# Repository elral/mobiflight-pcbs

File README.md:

# mobiflight-pcbs
PCBs and breakout boards, designed by the MobiFlight community:

* [MobiFlight Prototyping Board](prototyping-board/README.md)
* [MobiFlight Multiplexer Breakout Board](breakout-multiplexer/README.md)
* [MobiFlight MAX7219 Breakout System](max7219-breakout-system/README.md)
* [MobiFlight MAX7219 Adapter Board](max7219-adapter/README.md)
* [MobiFlight Dual Encoder Board](dual-encoder-board/README.md)
* [MobiFlight LED Driver Board](dual-encoder-board/README.md)

If you are missing information, or if you found a bug, please [create a new issue here on GitHub](https://github.com/MobiFlight/mobiflight-pcbs/issues/new).

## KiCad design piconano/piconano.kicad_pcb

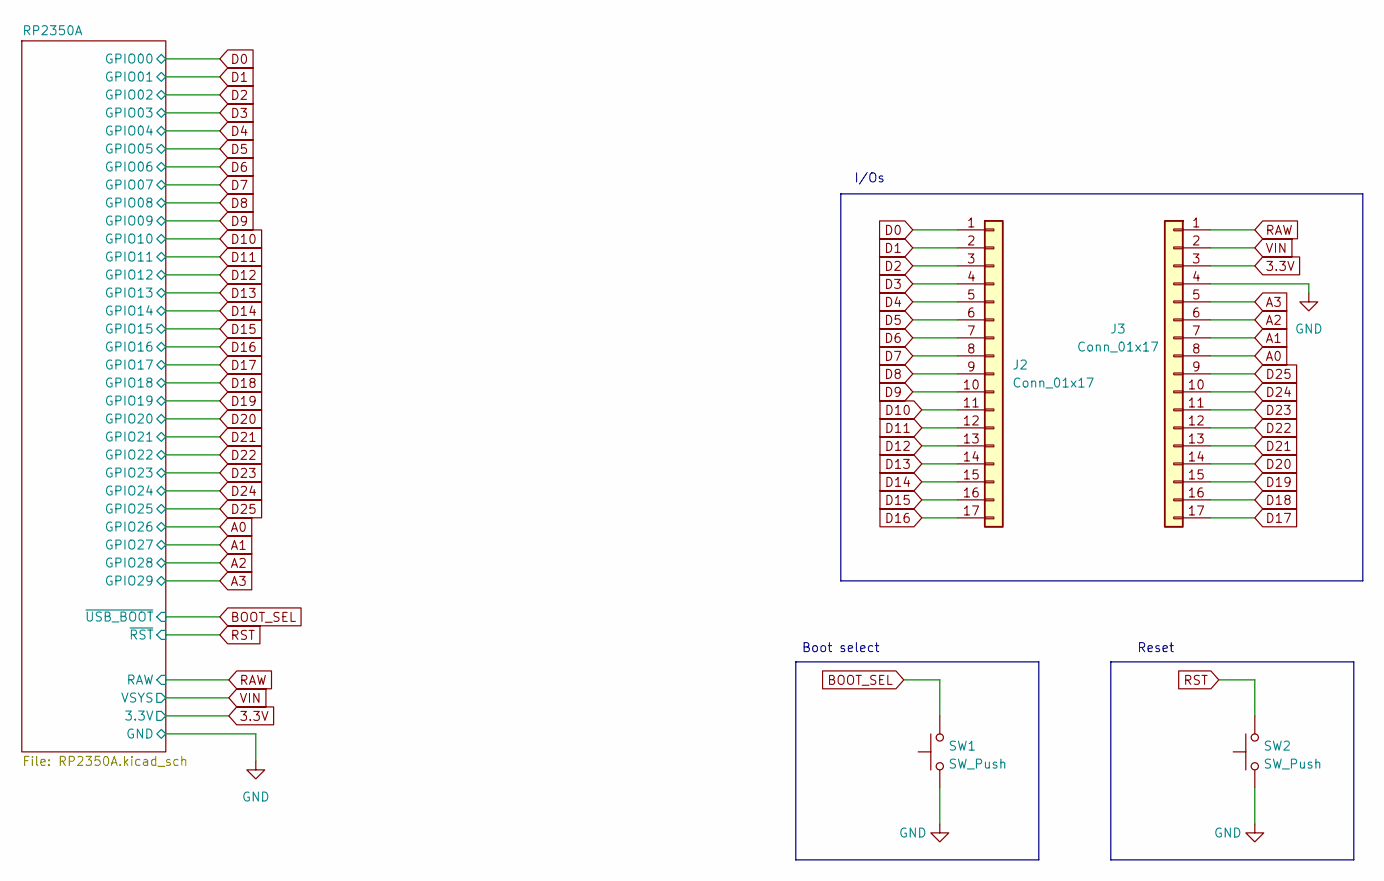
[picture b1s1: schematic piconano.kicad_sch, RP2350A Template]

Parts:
J2, J3: Conn_01x17; PinHeader_1x17_P2.54mm_Vertical
SW1, SW2: SW_Push; SW_Push_1P1T_NO_Vertical_Wuerth_434133025816; LCSC C92589

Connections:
3.3V: J3.3; also elsewhere on the board
A0: J3.8; also elsewhere on the board
A1: J3.7; also elsewhere on the board
A2: J3.6; also elsewhere on the board
A3: J3.5; also elsewhere on the board
BOOT_SEL: SW1.2; also elsewhere on the board
D0: J2.1; also elsewhere on the board
D1: J2.2; also elsewhere on the board
D2: J2.3; also elsewhere on the board
D3: J2.4; also elsewhere on the board
D4: J2.5; also elsewhere on the board
D5: J2.6; also elsewhere on the board
D6: J2.7; also elsewhere on the board
D7: J2.8; also elsewhere on the board
D8: J2.9; also elsewhere on the board
D9: J2.10; also elsewhere on the board
D10: J2.11; also elsewhere on the board
D11: J2.12; also elsewhere on the board
D12: J2.13; also elsewhere on the board
D13: J2.14; also elsewhere on the board
D14: J2.15; also elsewhere on the board
D15: J2.16; also elsewhere on the board
D16: J2.17; also elsewhere on the board
D17: J3.17; also elsewhere on the board
D18: J3.16; also elsewhere on the board
D19: J3.15; also elsewhere on the board
D20: J3.14; also elsewhere on the board
D21: J3.13; also elsewhere on the board
D22: J3.12; also elsewhere on the board
D23: J3.11; also elsewhere on the board
D24: J3.10; also elsewhere on the board
D25: J3.9; also elsewhere on the board
GND: J3.4, SW1.1, SW2.1; also elsewhere on the board
RAW: J3.1; also elsewhere on the board
RST: SW2.2; also elsewhere on the board
VIN: J3.2; also elsewhere on the board

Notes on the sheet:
Reset
Boot select
I/Os

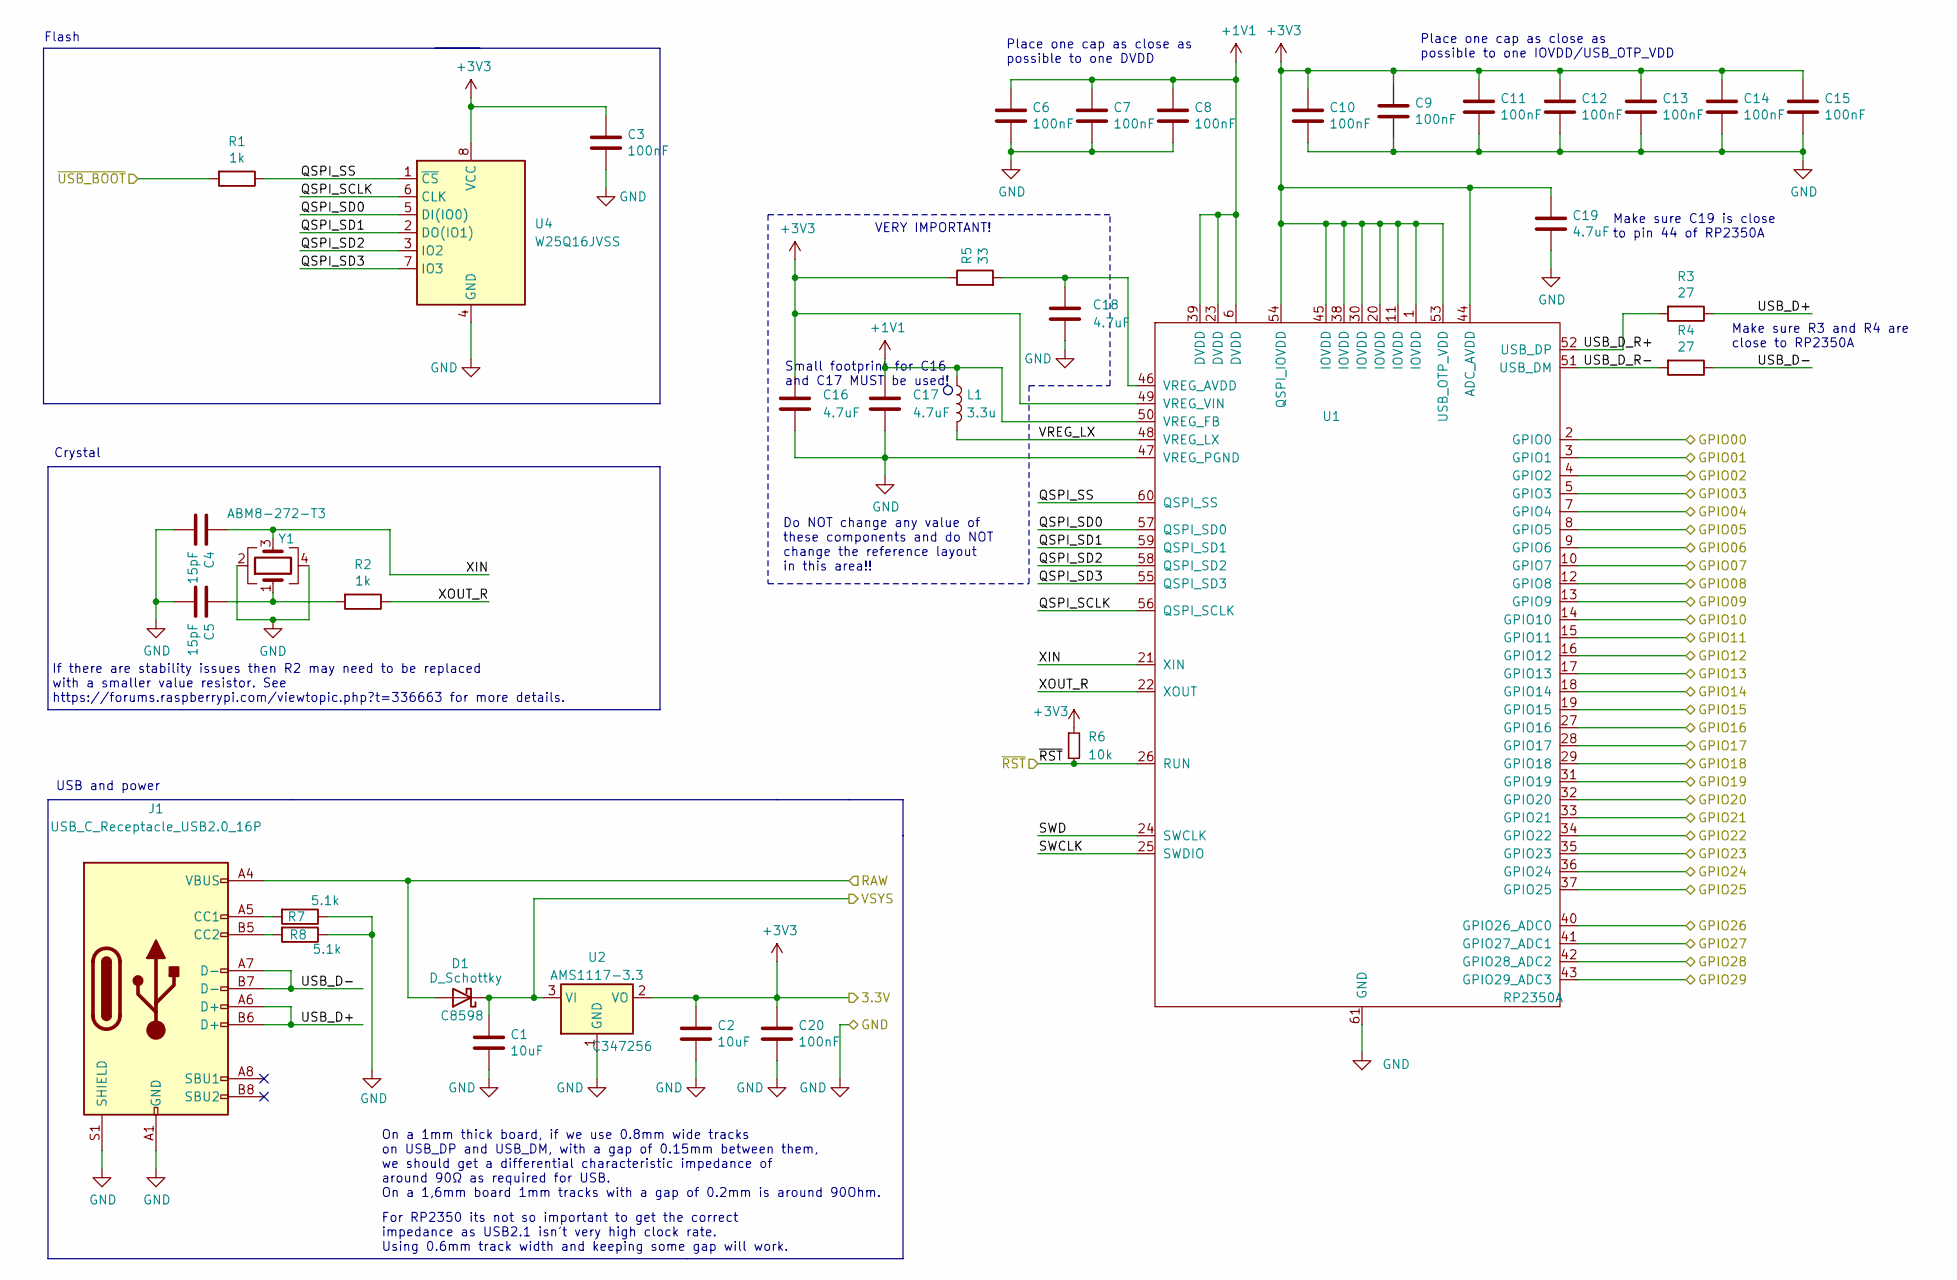
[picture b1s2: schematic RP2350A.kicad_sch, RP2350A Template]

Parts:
C1, C2: 10uF; C_0402_1005Metric; LCSC C15525
C3, C6, C7, C8, C9, C10, C11, C12, C13, C14, C15, C20: 100nF; C_0402_1005Metric; LCSC C1525
C4, C5: 15pF; C_0402_1005Metric; LCSC C1548
C16, C17: 4.7uF; C_0402_1005Metric_small_pads; LCSC C23733
C18, C19: 4.7uF; C_0402_1005Metric; LCSC C23733
D1: D_Schottky; D_SOD-123; LCSC C8598
J1: USB_C_Receptacle_USB2.0_16P; USB_C_Receptacle_HCTL_HC-TYPE-C-16P-01A; LCSC C2997432
L1: 3.3u; L_pol_2016; LCSC C42411119
R1, R2: 1k; R_0402_1005Metric; LCSC C11702
R3, R4: 27; R_0402_1005Metric; LCSC C25100
R5: 33; R_0402_1005Metric; LCSC C25105
R6: 10k; R_0402_1005Metric; LCSC C25744
R7, R8: 5.1k; R_0402_1005Metric; LCSC C25905
U1: RP2350A; RP2350A_QFN-60_EP_7.75x7.75_Pitch0.4mm; LCSC C42411118
U2: AMS1117-3.3; SOT-89-3; LCSC C347256
U4: W25Q16JVSS; Winbond_USON-8-1EP_3x2mm_P0.5mm_EP0.2x1.6mm; LCSC C2843335
Y1: ABM8-272-T3; Crystal_SMD_3225-4Pin_3.2x2.5mm; LCSC C20625731

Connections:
3.3V: C2.1, C3.1, C9.1, C10.1, C11.1, C12.1, C13.1, C14.1, C15.1, C16.1, C19.1, C20.1, R5.1, R6.1, U1.1 (IOVDD), U1.11 (IOVDD), U1.20 (IOVDD), U1.30 (IOVDD), U1.38 (IOVDD), U1.44 (ADC_AVDD), U1.45 (IOVDD), U1.49 (VREG_VIN), U1.53 (USB_OTP_VDD), U1.54 (QSPI_IOVDD), U2.2 (VO), U4.8 (VCC); also elsewhere on the board
+1V1: C6.1, C7.1, C8.1, C17.1, L1.1, U1.6 (DVDD), U1.23 (DVDD), U1.39 (DVDD), U1.50 (VREG_FB)
/RP2350A/QSPI_SCLK: U1.56 (QSPI_SCLK), U4.6 (CLK)
/RP2350A/QSPI_SD0: U1.57 (QSPI_SD0), U4.5 (DI(IO0))
/RP2350A/QSPI_SD1: U1.59 (QSPI_SD1), U4.2 (DO(IO1))
/RP2350A/QSPI_SD2: U1.58 (QSPI_SD2), U4.3 (IO2)
/RP2350A/QSPI_SD3: U1.55 (QSPI_SD3), U4.7 (IO3)
/RP2350A/QSPI_SS: R1.1, U1.60 (QSPI_SS), U4.1 (~CS)
/RP2350A/SWCLK: U1.25 (SWDIO)
/RP2350A/SWD: U1.24 (SWCLK)
/RP2350A/USB_D+: J1.A6 (D+), J1.B6 (D+), R3.1
/RP2350A/USB_D-: J1.A7 (D-), J1.B7 (D-), R4.1
/RP2350A/USB_D_R+: R3.2, U1.52 (USB_DP)
/RP2350A/USB_D_R-: R4.2, U1.51 (USB_DM)
/RP2350A/VREG_LX: L1.2, U1.48 (VREG_LX)
/RP2350A/XIN: C4.1, U1.21 (XIN), Y1.3
/RP2350A/XOUT_R: R2.1, U1.22 (XOUT)
A0: U1.40 (GPIO26_ADC0); also elsewhere on the board
A1: U1.41 (GPIO27_ADC1); also elsewhere on the board
A2: U1.42 (GPIO28_ADC2); also elsewhere on the board
A3: U1.43 (GPIO29_ADC3); also elsewhere on the board
BOOT_SEL: R1.2; also elsewhere on the board
D0: U1.2 (GPIO0); also elsewhere on the board
D1: U1.3 (GPIO1); also elsewhere on the board
D2: U1.4 (GPIO2); also elsewhere on the board
D3: U1.5 (GPIO3); also elsewhere on the board
D4: U1.7 (GPIO4); also elsewhere on the board
D5: U1.8 (GPIO5); also elsewhere on the board
D6: U1.9 (GPIO6); also elsewhere on the board
D7: U1.10 (GPIO7); also elsewhere on the board
D8: U1.12 (GPIO8); also elsewhere on the board
D9: U1.13 (GPIO9); also elsewhere on the board
D10: U1.14 (GPIO10); also elsewhere on the board
D11: U1.15 (GPIO11); also elsewhere on the board
D12: U1.16 (GPIO12); also elsewhere on the board
D13: U1.17 (GPIO13); also elsewhere on the board
D14: U1.18 (GPIO14); also elsewhere on the board
D15: U1.19 (GPIO15); also elsewhere on the board
D16: U1.27 (GPIO16); also elsewhere on the board
D17: U1.28 (GPIO17); also elsewhere on the board
D18: U1.29 (GPIO18); also elsewhere on the board
D19: U1.31 (GPIO19); also elsewhere on the board
D20: U1.32 (GPIO20); also elsewhere on the board
D21: U1.33 (GPIO21); also elsewhere on the board
D22: U1.34 (GPIO22); also elsewhere on the board
D23: U1.35 (GPIO23); also elsewhere on the board
D24: U1.36 (GPIO24); also elsewhere on the board
D25: U1.37 (GPIO25); also elsewhere on the board
GND: C1.2, C2.2, C3.2, C4.2, C5.2, C6.2, C7.2, C8.2, C9.2, C10.2, C11.2, C12.2, C13.2, C14.2, C15.2, C16.2, C17.2, C18.2, C19.2, C20.2, J1.A1 (GND), J1.A12 (GND), J1.B1 (GND), J1.B12 (GND), J1.S1 (SHIELD), R7.1, R8.1, U1.47 (VREG_PGND), U1.61 (GND), U2.1 (GND), U4.4 (GND), Y1.2, Y1.4; also elsewhere on the board
unnamed: C5.1, R2.2, Y1.1
unnamed: J1.A5 (CC1), R7.2
unnamed: J1.B5 (CC2), R8.2
unnamed: C18.1, R5.2, U1.46 (VREG_AVDD)
RAW: D1.2 (A), J1.A4 (VBUS), J1.A9 (VBUS), J1.B4 (VBUS), J1.B9 (VBUS); also elsewhere on the board
RST: R6.2, U1.26 (RUN); also elsewhere on the board
VIN: C1.1, D1.1 (K), U2.3 (VI); also elsewhere on the board

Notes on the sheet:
USB and power
Small footprint for C16 and C17 MUST be used!
If there are stability issues then R2 may need to be replaced with a smaller value resistor. See https://forums.raspberrypi.com/viewtopic.php?t=336663 for more details.
Make sure R3 and R4 are close to RP2350A
Crystal
Make sure C19 is close to pin 44 of RP2350A
On a 1mm thick board, if we use 0.8mm wide tracks on USB_DP and USB_DM, with a gap of 0.15mm between them, we should get a differential characteristic impedance of around 90Ω as required for USB. On a 1,6mm board 1mm tracks with a gap of 0.2mm is around 90Ohm.
Place one cap as close as possible to one IOVDD/USB_OTP_VDD
For RP2350 its not so important to get the correct impedance as USB2.1 isn't very high clock rate. Using 0.6mm track width and keeping some gap will work.
VERY IMPORTANT!
Flash
Place one cap as close as possible to one DVDD
Do NOT change any value of these components and do NOT change the reference layout in this area!!

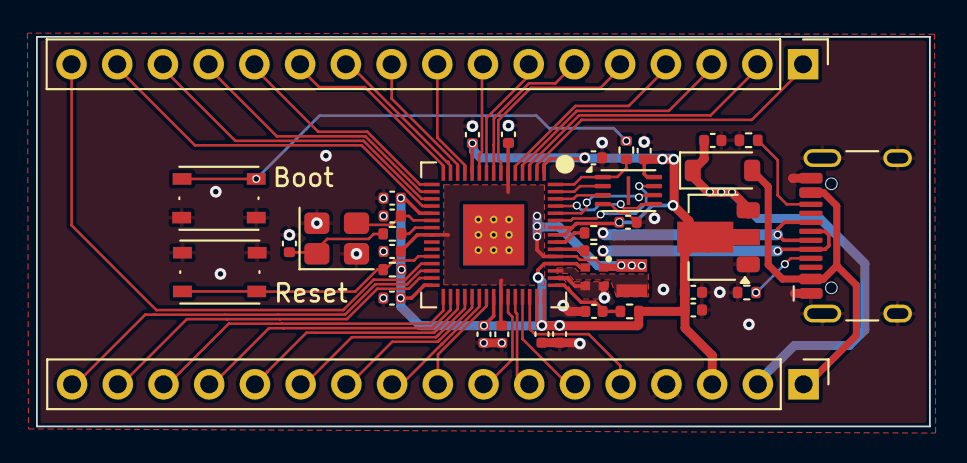
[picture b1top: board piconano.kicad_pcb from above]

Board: 2 copper layers, 49.6 x 21.6 mm, 39 parts (0 on the bottom side), 54 nets.

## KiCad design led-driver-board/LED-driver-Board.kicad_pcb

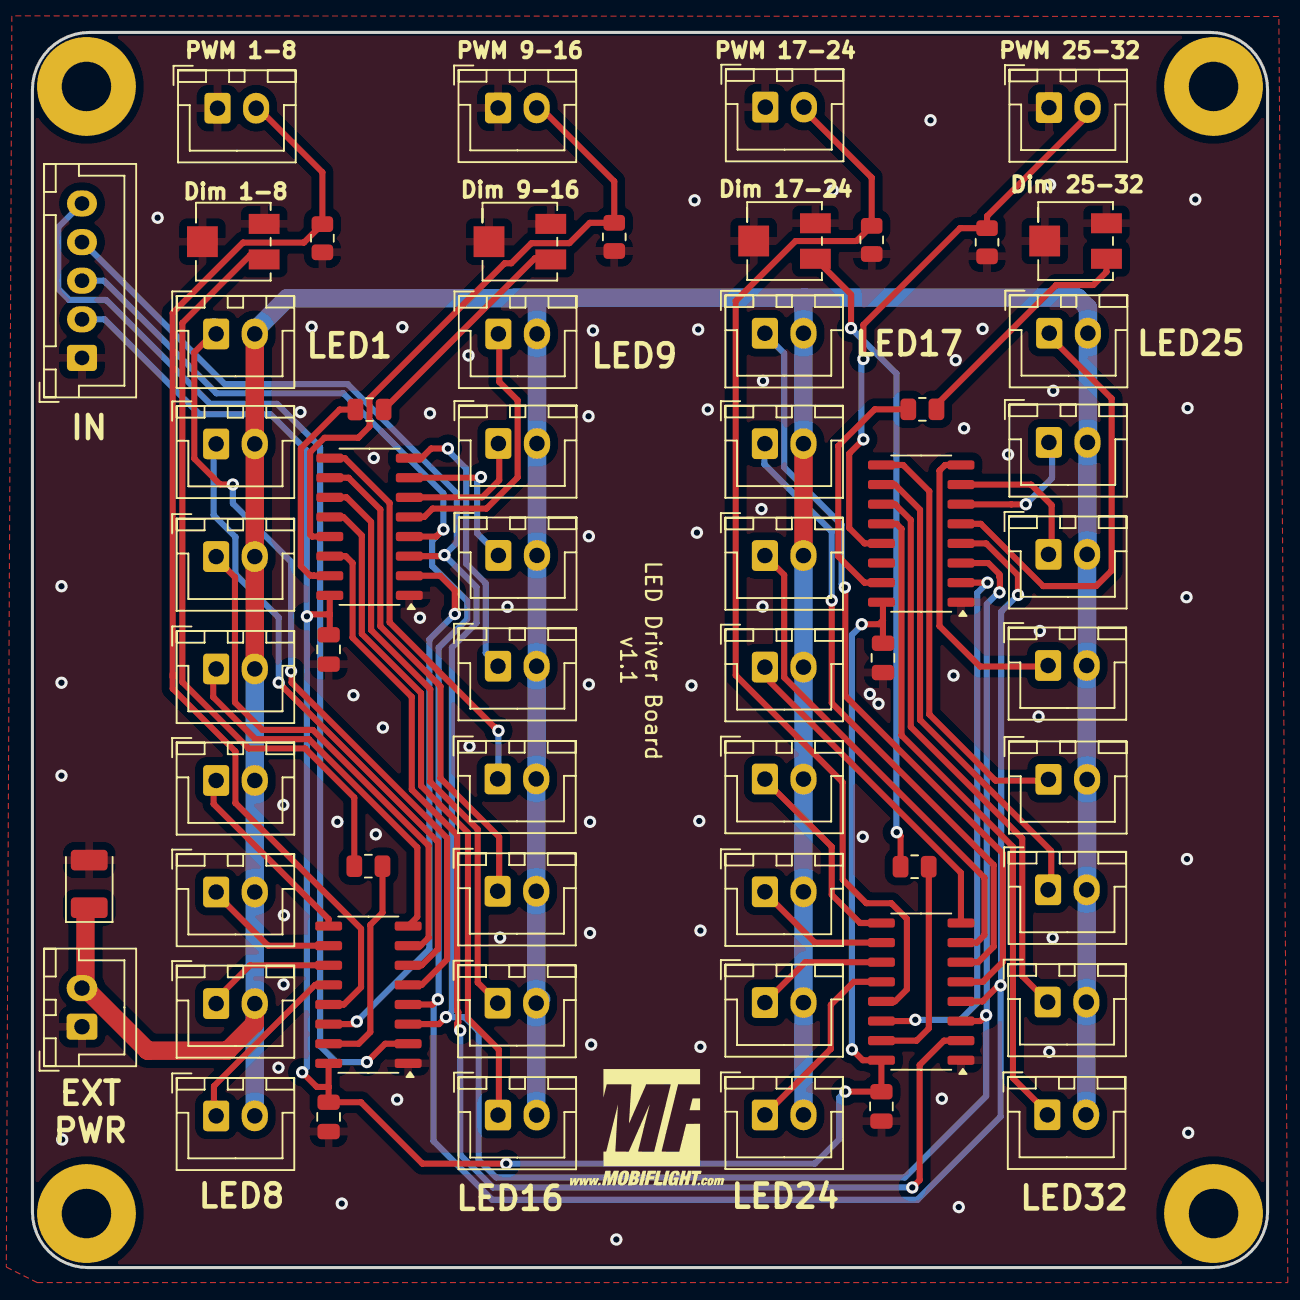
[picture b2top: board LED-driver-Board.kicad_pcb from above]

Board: 2 copper layers, 80.0 x 80.0 mm, 65 parts (1 on the bottom side), 53 nets.

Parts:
C1, C2, C3, C4: 100n; C_0805_2012Metric
C5: 47u; CP_EIA-3528-21_Kemet-B
G2, G2#2: LOGO; MobiFlight-Logo-Small
H1, H2, H3, H4: MountingHole; MountingHole_3.2mm_M3_Pad
J1: LED1; JST_XH_B2B-XH-A_1x02_P2.50mm_Vertical
J2: LED2; JST_XH_B2B-XH-A_1x02_P2.50mm_Vertical
J3: LED3; JST_XH_B2B-XH-A_1x02_P2.50mm_Vertical
J4: LED4; JST_XH_B2B-XH-A_1x02_P2.50mm_Vertical
J5: LED5; JST_XH_B2B-XH-A_1x02_P2.50mm_Vertical
J6: LED6; JST_XH_B2B-XH-A_1x02_P2.50mm_Vertical
J7: LED7; JST_XH_B2B-XH-A_1x02_P2.50mm_Vertical
J8: LED8; JST_XH_B2B-XH-A_1x02_P2.50mm_Vertical
J9: LED9; JST_XH_B2B-XH-A_1x02_P2.50mm_Vertical
J10: LED10; JST_XH_B2B-XH-A_1x02_P2.50mm_Vertical
J11: LED11; JST_XH_B2B-XH-A_1x02_P2.50mm_Vertical
J12: LED12; JST_XH_B2B-XH-A_1x02_P2.50mm_Vertical
J13: LED13; JST_XH_B2B-XH-A_1x02_P2.50mm_Vertical
J14: LED14; JST_XH_B2B-XH-A_1x02_P2.50mm_Vertical
J15: LED15; JST_XH_B2B-XH-A_1x02_P2.50mm_Vertical
J16: LED16; JST_XH_B2B-XH-A_1x02_P2.50mm_Vertical
J17: LED17; JST_XH_B2B-XH-A_1x02_P2.50mm_Vertical
J18: LED18; JST_XH_B2B-XH-A_1x02_P2.50mm_Vertical
J19: LED19; JST_XH_B2B-XH-A_1x02_P2.50mm_Vertical
J20: LED20; JST_XH_B2B-XH-A_1x02_P2.50mm_Vertical
J21: LED21; JST_XH_B2B-XH-A_1x02_P2.50mm_Vertical
J22: LED22; JST_XH_B2B-XH-A_1x02_P2.50mm_Vertical
J23: LED23; JST_XH_B2B-XH-A_1x02_P2.50mm_Vertical
J24: LED24; JST_XH_B2B-XH-A_1x02_P2.50mm_Vertical
J25: LED25; JST_XH_B2B-XH-A_1x02_P2.50mm_Vertical
J26: LED26; JST_XH_B2B-XH-A_1x02_P2.50mm_Vertical
J27: LED27; JST_XH_B2B-XH-A_1x02_P2.50mm_Vertical
J28: LED28; JST_XH_B2B-XH-A_1x02_P2.50mm_Vertical
J29: LED29; JST_XH_B2B-XH-A_1x02_P2.50mm_Vertical
J30: LED30; JST_XH_B2B-XH-A_1x02_P2.50mm_Vertical
J31: LED31; JST_XH_B2B-XH-A_1x02_P2.50mm_Vertical
J32: LED32; JST_XH_B2B-XH-A_1x02_P2.50mm_Vertical
J33, J34, J35, J36: JST-XH_02_Pin_vertical; JST_XH_B2B-XH-A_1x02_P2.50mm_Vertical
J102: PWR; JST_XH_B2B-XH-A_1x02_P2.50mm_Vertical
J103: Dim; JST_XH_B5B-XH-A_1x05_P2.50mm_Vertical
R1, R2, R3, R4: 100; R_0805_2012Metric
R5, R6, R7, R8: 1k; R_0805_2012Metric
RV1, RV2, RV3, RV4: 5k; Potentiometer_Bourns_3214J_Horizontal
U1, U2, U3, U4: STP08DP05MTR; SO-16_3.9x9.9mm_P1.27mm

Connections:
+5V: C1.2, C2.2, C3.2, C4.2, J103.2, U1.16 (VDD), U2.16 (VDD), U3.16 (VDD), U4.16 (VDD)
CLK: J103.4, U1.3 (CLK), U2.3 (CLK), U3.3 (CLK), U4.3 (CLK)
GND: C1.1, C2.1, C3.1, C4.1, C5.2, J33.1, J34.1, J35.1, J36.1, J102.1, J103.1, R5.1, R6.1, R7.1, R8.1, RV1.1, RV1.2, RV2.1, RV2.2, RV3.1, RV3.2, RV4.1, RV4.2, U1.1 (GND), U2.1 (GND), U3.1 (GND), U4.1 (GND)
LATCH: J103.3, U1.4 (LE(ED1)), U2.4 (LE(ED1)), U3.4 (LE(ED1)), U4.4 (LE(ED1))
LED1: J1.1, U1.5 (~OUT0)
LED2: J2.1, U1.6 (~OUT1)
LED3: J3.1, U1.7 (~OUT2)
LED4: J4.1, U1.8 (~OUT3)
LED5: J5.1, U1.9 (~OUT4)
LED6: J6.1, U1.10 (~OUT5)
LED7: J7.1, U1.11 (~OUT6)
LED8: J8.1, U1.12 (~OUT7)
LED9: J9.1, U2.5 (~OUT0)
LED10: J10.1, U2.6 (~OUT1)
LED11: J11.1, U2.7 (~OUT2)
LED12: J12.1, U2.8 (~OUT3)
LED13: J13.1, U2.9 (~OUT4)
LED14: J14.1, U2.10 (~OUT5)
LED15: J15.1, U2.11 (~OUT6)
LED16: J16.1, U2.12 (~OUT7)
LED17: J17.1, U3.5 (~OUT0)
LED18: J18.1, U3.6 (~OUT1)
LED19: J19.1, U3.7 (~OUT2)
LED20: J20.1, U3.8 (~OUT3)
LED21: J21.1, U3.9 (~OUT4)
LED22: J22.1, U3.10 (~OUT5)
LED23: J23.1, U3.11 (~OUT6)
LED24: J24.1, U3.12 (~OUT7)
LED25: J25.1, U4.5 (~OUT0)
LED26: J26.1, U4.6 (~OUT1)
LED27: J27.1, U4.7 (~OUT2)
LED28: J28.1, U4.8 (~OUT3)
LED29: J29.1, U4.9 (~OUT4)
LED30: J30.1, U4.10 (~OUT5)
LED31: J31.1, U4.11 (~OUT6)
LED32: J32.1, U4.12 (~OUT7)
unnamed: R1.1, RV1.3
unnamed: R2.1, RV2.3
unnamed: R3.1, RV3.3
unnamed: R4.1, RV4.3
unnamed: R1.2, U1.15 (R-EXT)
unnamed: U1.14 (SDO), U2.2 (SDI)
unnamed: R2.2, U2.15 (R-EXT)
unnamed: U2.14 (SDO), U3.2 (SDI)
unnamed: R3.2, U3.15 (R-EXT)
unnamed: U3.14 (SDO), U4.2 (SDI)
unnamed: R4.2, U4.15 (R-EXT)
OE1: J33.2, R5.2, U1.13 (~OE(ED2))
OE2: J34.2, R6.2, U2.13 (~OE(ED2))
OE3: J35.2, R7.2, U3.13 (~OE(ED2))
OE4: J36.2, R8.2, U4.13 (~OE(ED2))
SDI: J103.5, U1.2 (SDI)
VDC: C5.1, J1.2, J2.2, J3.2, J4.2, J5.2, J6.2, J7.2, J8.2, J9.2, J10.2, J11.2, J12.2, J13.2, J14.2, J15.2, J16.2, J17.2, J18.2, J19.2, J20.2, J21.2, J22.2, J23.2, J24.2, J25.2, J26.2, J27.2, J28.2, J29.2, J30.2, J31.2, J32.2, J102.2

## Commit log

2025-07-23 add led driver board V1.1
2025-07-24 new IN and PWR connector position, update fabrication files
2025-07-24 update position of mounting holes, update fabrication files
2025-07-25 add input shifter board
2025-10-31 add PicoNano first version
2025-11-20 Revert "add PicoNano first version"
    This reverts commit 719eee0f06b7e31952d5c34a1e040bb831883a96.
